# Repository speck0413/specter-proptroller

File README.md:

# Specter Proptroller

An all-in-one, open-source controller for props, animatronics and show effects. One 134 x 80 mm board takes a plug-in
microcontroller (a 30-pin ESP32 DevKit **or** a Raspberry Pi Pico / Pico W / Pico 2 / Pico 2 W; a plain Pico 2 has no firmware build yet) and gives it the I/O a prop needs:

| Block | What it does |
|---|---|
| 4 power outputs (OUT1-4) | high-side switched supply voltage, 5 A each continuous at 12-24 V (7.5 A for 5 s at low duty from idle, 10 A start-up surge under 1 s; 10 A board total); PWM dimming and soft start up to 2 A at 12 V (1 A at 24 V); LED per output |
| 2 relays (RLY1-2) | dry COM / NO / NC contacts. Rev B: **120 V AC 5 A (3 A inductive) or 28 V DC 10 A**; rev A: **≤30 V DC only** |
| Trigger inputs (TRIG1, TRIG2) | 3.5 mm TRS jacks: contact closure or a small powered sensor (3.3 V on the ring) |
| Contact outputs (CONTACT1-2; CC1-2 in scripts and code) | isolated optocoupler closures on 3.5 mm jacks, to trigger other controllers or devices: signals only, ≤30 V DC, plan on about 2 mA, tip + / sleeve − |
| Pixels | 5 V level-shifted data for addressable LED strips |
| Audio | DFPlayer Mini MP3 module (two-way UART), speaker terminal and stereo line out |
| Buttons | three on-board user buttons |
| Expansion | 3 x 11 servo-style S/V/G header (I2C, analog, spare GPIOs), RAILS power terminal for accessories |
| Power | 9-24 V DC in (barrel ≤5 A or terminal ≤10 A), on-board 5 V / 2.5 A buck, TVS protection. Ratings are for a 12-24 V supply (12 V is the primary use case); below 12 V (down to the 9 V minimum), derate: the OUT FETs see less gate drive and run hotter |

Controllers can be cascaded: a CONTACT output or a relay of one board triggers the TRIG1 / TRIG2 input of another, so one
controller can drive up to four others; ESP-NOW / Wi-Fi is the option for richer coordination.

## Getting started

New here? **[GETTING-STARTED.md](GETTING-STARTED.md)** goes from the parts on your table to a running prop with no
programming: what to buy, flashing the stock firmware from the browser (ESP32) or by copying one file (Pico W),
the sound card, wiring, and your first effect script typed on your phone. Then:

- [firmware/SHOW-SCRIPT.md](firmware/SHOW-SCRIPT.md): the effect script language (nine kinds of line), and
  [firmware/show-script-examples/](firmware/show-script-examples/) with wiring notes;
- [the Arduino library](firmware/arduino/lib/proptroller/README.md): effects in code;
- [hardware/README.md](hardware/README.md): ratings, pinout and power.
- [firmware/BARE-DEVKIT.md](firmware/BARE-DEVKIT.md): no board yet? Run the firmware on a bare ESP32 DevKit,
  ESP32-S3 DevKit or ESP32-C3 SuperMini (outputs through MOSFET or relay modules).
- [studio/](studio/README.md): **Specter Studio**, the desktop app for these boards (Windows, macOS, Linux):
  find boards, write effects as text or blocks, try them on a practice board, update firmware, copy sounds to the
  SD card. Installers are on the [releases page](https://github.com/speck0413/specter-proptroller/releases)
  (`studio-v…` tags).
- [docs/DEV-SETUP.md](docs/DEV-SETUP.md): from nothing to a running board with Specter Studio built from
  source (macOS, with Windows and Linux notes): the setup script, the clone, a USB install and a script.
- [docs/FIRMWARE-BUILD.md](docs/FIRMWARE-BUILD.md): build the firmware for each board, flash it over USB, make a
  release folder, update over Wi-Fi, and what CI does on a release tag.

## Status

This repository holds hardware rev B (relay insulation margin and air-gap slots for a 120 V AC relay rating, see
`hardware/README.md`), not yet ordered. Rev A, the first ordered design (silk "RELAYS: <=30V DC ONLY"; not yet built or
tested), differs as `hardware/README.md` describes (ratings, relay positions, errata).
A 3D-printed enclosure is in `enclosure/` (not printed yet).
Firmware: C++ on the Arduino cores with PlatformIO (`firmware/arduino`), tested on the host and in a simulator; not yet run on a
board. The desktop app, Specter Studio, is in `studio/`. Wiring guides and a build guide are in `docs/` (below).

## What is here

| Path | Contents |
|---|---|
| `hardware/board.ts` | the board, written as design intent for the [aieda](https://github.com/speck0413/ai-native-eda) toolchain (parts, nets, placement constraints, routing classes) |
| `hardware/frozen.ts`, `hardware/routes.ts` | the reviewed part placement and locked routing, so every build reproduces the same board |
| `hardware/lib/parts.ts` | the parts this board uses (KiCad footprints, LCSC numbers, pad maps checked against datasheets) |
| `hardware/requirements.yaml` | requirements with ids traced by the build |
| `hardware/README.md` | ratings, GPIO map, power budget, copper sizing, test pads and first-board checks |
| `enclosure/` | the 3D-printed enclosure: OpenSCAD model, `design.toml` with every size, Bambu Studio projects, build and check tools |
| `GETTING-STARTED.md` | from a new board to a running prop, no programming |
| `firmware/` | the firmware (`arduino/`), the protocol (`PROTOCOL.md`), flash maps, the phone web UI (`web/`) and its browser tests (`web-test/`), golden sets and example show scripts |
| `studio/` | Specter Studio, the desktop app (Tauri: Rust device layer in `core/`, React app in `src/`, Playwright tests in `tests/e2e/`); it builds its practice board from `firmware/` and bundles the firmware library and the wiring guides. See [studio/README.md](studio/README.md) and [studio/docs/BUILDING.md](studio/docs/BUILDING.md) |
| `.github/workflows/` | `firmware.yml`: firmware host tests, board builds, examples, simulator and phone-page browser tests (on changes to `firmware/`); `firmware-release.yml`: on a tag `v<firmware/VERSION>`, builds the stock firmware (ESP32 DevKit, Pico W, Pico 2 W, and the bare devkits), drafts a GitHub Release with the update and first-flash images and `proptroller-firmware.json`, and publishes the browser flasher to GitHub Pages; `studio.yml`: Studio's tests and e2e (on changes to `studio/` or `firmware/`), the installers (on changes to `studio/`), and on a tag `studio-v<version>` the installers on that tag's release |
| `docs/` | wiring guides (interactive 3D pages, written pages, videos), the case build guide, switching AC loads, developer setup with Specter Studio (`DEV-SETUP.md`), building and flashing the firmware (`FIRMWARE-BUILD.md`) |
| `tools/` | `setup.sh` (firmware setup; `--dev` for the developer checks; Studio has its own, `studio/scripts/setup.sh`), bootstrap, JLC order packages (with rotation corrections), routing helpers |

The generated KiCad project (`hardware/kicad/`: board, schematic, rules, symbol library, build records) and the order files
(`hardware/fab/`: gerbers zip, BOM, CPL, three JLC packages) are committed, so you can open or order the board without building it.
Regenerating takes a few minutes and runs `tools/portable_paths.py` so the files carry no machine-specific paths.

## Developer quick start (VS Code)

For changing the firmware itself. To use a board, [GETTING-STARTED.md](GETTING-STARTED.md) is enough; to write
effects in code, start with [the library's README](firmware/arduino/lib/proptroller/README.md).

1. Clone and set up (Linux or macOS; Windows: see [Windows](#windows) below):
   ```sh
   git clone https://github.com/speck0413/specter-proptroller.git && cd specter-proptroller
   tools/setup.sh            # PlatformIO, a host compiler, the board packages; asks before sudo
   tools/setup.sh --dev      # optional: also clang-tidy, cppcheck, fuzzers, browser-test tools
   ```
   It offers (asking first) to put `pio` on your PATH and, on Linux, the serial-port access (the `dialout`
   group and PlatformIO's udev rules; log out and in afterwards).
2. Open it: `code spectre-proptroller.code-workspace`, then click **Install** when VS Code offers the
   recommended extensions (PlatformIO IDE, C/C++, EditorConfig, Markdown lint, spell checker, WSL).
3. Wait for PlatformIO to finish loading (status bar), then **Terminal > Run Task**:
   - **Native unit tests**: the host tests (no board needed).
   - **Host simulator**: a simulated board; open <http://localhost:8080/> for its phone page.
   - **Build all boards**: ESP32 DevKit, Pico, Pico W, Pico 2 W, and the bare devkits (ESP32, ESP32-S3, ESP32-C3 SuperMini).
4. Flash a board (USB):
   - ESP32 DevKit: `cd firmware/arduino && pio run -e esp32dev -t upload`
   - Pico (no Wi-Fi): `cd firmware/arduino && pio run -e pico -t upload` (the first time, hold BOOTSEL while
     plugging it in). It is updated over USB only.
   - Pico W / Pico 2 W (first time): run the task **Pico W / Pico 2 W first-flash file**, hold BOOTSEL, plug in,
     copy `firmware/arduino/.pio/build/picoboot-pico-w/flash.uf2` (Pico 2 W: `picoboot-pico2-w`) to the drive.
     After that, update over Wi-Fi from the board's page.
5. Change something: your own firmware starts from `firmware/arduino/workspace-template/`; effects without code are show
   scripts (`firmware/show-script-examples/`). Writing sketches: [the library's README](firmware/arduino/lib/proptroller/README.md);
   how the firmware is built and tested: [firmware/arduino/README.md](firmware/arduino/README.md).

### Windows

Two ways, both with VS Code:

- **Native (simplest for building and flashing boards):** install [VS Code](https://code.visualstudio.com/), then the
  **PlatformIO IDE** extension (it installs PlatformIO and its Python by itself), and open
  `spectre-proptroller.code-workspace`. The tasks **Build all boards** and **Pico W / Pico 2 W first-flash file** and
  PlatformIO's own Upload button work in it. Install the USB driver your ESP32 DevKit needs (Silicon Labs CP210x or
  WCH CH340). The host unit tests and the simulator also need a C++ compiler for Windows (for example MSYS2's
  MinGW-w64 g++ on PATH; the simulator is `pio run -e sim_win`, without MQTT); the tasks that are shell scripts (static check, fuzzers, browser tests, QEMU, golden
  files) need WSL 2.
- **WSL 2 (everything):** install WSL 2 with Ubuntu (`wsl --install` in an administrator PowerShell), install the
  **WSL** extension in VS Code, open the folder with **WSL: Open Folder in WSL**, and run `tools/setup.sh` in its
  terminal. WSL does not see USB by itself: install [usbipd-win](https://github.com/dorssel/usbipd-win) in Windows,
  then `usbipd list`, `usbipd bind --busid <id>` (once, administrator) and `usbipd attach --wsl --busid <id>` each
  time the board is plugged in.

### If something goes wrong

- **The page says `rolled_back`**: the new firmware did not pass its self-check and the board went back to the
  one before. Your settings are as they were; try the update again or report it.
- **A Pico W that will not stay up** (restarts every few seconds): flash it again over USB (hold BOOTSEL, copy
  the first-flash file). Re-flashing keeps the settings, shows and script; if it still restarts (a saved setting
  such as an unreachable Wi-Fi), erase everything as below and set it up again.
- **Start over, erasing everything** (settings, Wi-Fi, shows, script): Settings, Factory reset on the page, or
  over USB: Pico `picotool erase` (then flash again), ESP32 `pio run -e esp32dev -t erase` (or
  `esptool.py erase_flash`) and flash again.

## Specter Studio from source

```sh
git clone https://github.com/speck0413/specter-proptroller.git && cd specter-proptroller/studio
scripts/setup.sh          # Node.js, Rust, PlatformIO, Tauri's system parts; npm ci and the practice board
npm run tauri dev         # the desktop app
```

Windows uses `scripts\setup.ps1`. The step-by-step version is [docs/DEV-SETUP.md](docs/DEV-SETUP.md); tests,
desktop builds and the layout are in [studio/README.md](studio/README.md). Studio needs no submodule (the `aieda`
submodule is for the hardware build only).

## Releases

One repository, two kinds of tag:

| Tag | Workflow | Release |
|---|---|---|
| `v<firmware/VERSION>`, e.g. `v0.1.0-rc.3` | `firmware-release.yml` | a draft "Firmware v…" release with the images and `proptroller-firmware.json` (published by hand), and the browser flasher |
| `studio-v<version>`, e.g. `studio-v0.1.0-rc.3` (the version in `studio/package.json`, `studio/src-tauri/tauri.conf.json` and `studio/Cargo.toml`) | `studio.yml` | a "Specter Studio …" release with the installers and `SHA256SUMS.txt` |

A version with a suffix (`-rc.3`) makes a pre-release. Studio's firmware updates look only at releases that
carry `proptroller-firmware.json`, so Studio's own releases never count as firmware; GitHub's "Latest" label goes
to whichever full release is newest, so link the firmware by its tag. Details:
[docs/FIRMWARE-BUILD.md](docs/FIRMWARE-BUILD.md) (section 6) and [studio/docs/BUILDING.md](studio/docs/BUILDING.md).

## Build (hardware)

Requires KiCad 10 (with `kicad-cli`), Node.js, Python 3 and Java (for Freerouting).

```sh
git clone --recursive https://github.com/speck0413/specter-proptroller.git && cd specter-proptroller
tools/bootstrap.sh        # aieda submodule, its Node deps, Freerouting
make typecheck
make build                # KiCad project in hardware/kicad/ (about 4 minutes)
make fab order            # gerbers in hardware/fab/, JLC BOM/CPL packages in hardware/fab/order/
```

Always check JLC's placement preview before ordering.

The committed `hardware/kicad/proptroller.kicad_pcb` is the reference board. Every signal and power net is locked (`routes.ts`) and the
placement is pinned, so a rebuild reproduces the same tracks and vias with the toolchain it was made with: KiCad 10.0.6, Freerouting 2.5.0
(`tools/freerouting.pin`), aieda v0.2.0-1-gcd1f38a (submodule). Other tool versions may change the GND fanout or pour fill: compare before replacing it.

## Wiring guides

New to wiring? [docs/wiring-guides/](docs/wiring-guides/README.md) has a starter kit (a button, a motion sensor, a lamp,
a fan, a pixel strip and a speaker on one desk) and short guides for the common hookups, each as an interactive 3D page
with narration ([docs/wiring-guides/html/index.html](docs/wiring-guides/html/index.html), works offline), a written page,
and a renderable video. Assembling the board into its case: [docs/build-guide/](docs/build-guide/index.html) (written for rev A and an earlier case:
where it differs, `hardware/README.md` and `enclosure/README.md` are right).

## Safety

Read **[SAFETY.md](SAFETY.md)** first: the project is provided as-is, with no warranty and no certification, and you build
and use it at your own risk.

The board is powered from **low-voltage DC**: use a listed power supply with its own over-current protection (≤10 A); the board has
no fuses. The recommended way to switch AC loads is **off the board**, with a listed relay-controlled outlet box driven at low voltage
([docs/ac-control.md](docs/ac-control.md)). Only the rev B relays may switch AC directly, up to **120 V AC 5 A (3 A inductive)** each, only
from a GFCI-protected outlet, with a 5 A fuse in each relay's COM wire, and in the AC case with its earth leads on both earth holes (H2, H3). That rating rests on the relay's own insulation and a design margin
(≥3.0 mm copper clearance and air-gap slots around the relay contacts), not a certification; fog fluid residue, condensation and dust
degrade it over time, so keep the board clean and dry (`hardware/README.md`). Rev A relays are rated ≤30 V DC only: **AC on rev A relays is experimental, for prove-out only, not considered safe, and recommended against until rev B**.
Every other terminal, and every 3.5 mm jack, is low-voltage DC only. The board does not measure or limit current: keep each load
within its terminal's rating ([hardware/README.md](hardware/README.md)).

## License

MIT, see [LICENSE](LICENSE). The licence covers everything in this repository: the software (firmware, Specter
Studio, tools, web page), the hardware design files (`hardware/`, `enclosure/`) and the documentation. See also [SAFETY.md](SAFETY.md).

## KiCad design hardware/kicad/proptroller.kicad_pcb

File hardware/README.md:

# Spectre Proptroller board (rev B): ratings, pinout and power

134 x 80 mm, 2 layers. Silkscreen: "SPECTRE PROPTROLLER rev B" (rev A, the first ordered design, differs as this page says; this repo holds rev B). Plug-in MCU: a 30-pin ESP32 DevKit **or** a Raspberry Pi Pico family
board (never both). The bottom silkscreen carries a short version of this page.

Provided as-is, with no warranty and no certification; you build and use it at your own risk: read
[../SAFETY.md](../SAFETY.md) before wiring anything, and above all before mains on a rev B relay.

## Ratings at a glance

Ratings are for a **12-24 V supply** (12 V is the primary use case). Below 12 V (down to the 9 V minimum), derate: the OUT FETs see
less gate drive and run hotter.

| Item | Rating | Limit set by |
|---|---|---|
| Input (barrel DC-005) | 9-24 V DC, **5 A** | jack rating |
| Input (5.08 terminal, parallel) | 9-24 V DC, **10 A** board total | +VIN copper (3.5 mm class), supply OCP |
| Protection | SMAJ24A TVS only; **no fuses, no reverse-polarity FET** | design choice (accepted risk AR-1, rev B): use a listed supply with OCP, ≤10 A; it shuts itself off on overload |
| OUT1-4 (rev A and B) | switched +VIN (high side, AO4485), **5 A each continuous**; **7.5 A for 5 s at ≤2 % duty, starting from idle (the FET cool)**, both at **VIN 12-24 V** (e.g. once every 6 min; pending a first-board heat test; below 12 V derate); **10 A only as a start-up surge under ~1 s**; **sum of everything ≤10 A**; barrel input ≤5 A (use the terminal input above 5 A) | FET junction temperature (thermal note below), SS56 freewheel, copper |
| OUT1-4 PWM | ≤1 A at 24 V, ≤2 A at 12 V (slow 4.7k turn-off heats the FET) | FET switching loss |
| RLY1-2 (rev B) | dry COM / NO / NC, **120 V AC 5 A resistive (3 A inductive) or 28 V DC 10 A resistive** per relay ("120VAC 5A (3A IND) / 28VDC 10A"); derate for DC motors and solenoids | SRD-05 contacts (Songle datasheet, below) and the SAF-1 insulation margin (a design margin, not a certification); no fuse. Rev A: **≤30 V DC only** (table below) |
| +5V buck (TPS54360B) | **2.5 A** continuous | inductor, catch diodes, thermal |
| +3V3 | from the MCU module's regulator, **0.1 A** for board use | DevKit AMS1117 / Pico RT6150 headroom |
| RAILS out (5.08 5P) | VIN 3 A, 5V 0.1 A, 3V3 0.05 A | daisy-chain feed for a small accessory, not a second board |
| PIXEL | 5 V, ≤1 A from the board (≈16 WS2812 at full white); inject 5 V for longer strips. **No bulk capacitor on the board**: fit 470-1000 µF, ≥6.3 V across +5V / GND at the strip input, and plug or unplug the strip only with power off. The data output is inverted (2N7002 stage): the firmware inverts it | +5V budget |
| SPK | DFPlayer amplifier output, 3 W max into 4 Ω (bridge-tied: never ground either wire) | DFPlayer |
| TRIG1 / TRIG2 | 3.5 mm TRS: tip = input (3.3 V logic, closes to sleeve = active LOW), ring = 3V3 via 220 Ω (≤15 mA for a powered sensor), sleeve = GND | GPIO, 220 Ω |
| CONTACT1-2 | isolated optocoupler output (LTV-217) across tip (+) / sleeve (−): **≤30 V DC, ≤50 mA absolute maximum**, polarity matters; **count on about 2 mA** switched (note below) | LTV-217 (IC 50 mA, VCEO 70 V abs; CTR at the board's LED drive) |

**CONTACT1-2 current.** 50 mA is the LTV-217's absolute maximum, not what it is guaranteed to pass. The board drives the opto LED
with about 9 mA from an ESP32 and about 5-6 mA from a Pico (the RP2040 / RP2350 pads default to 4 mA drive and the firmware sets
none). Saturated (VCE(sat) 0.4 V max at IF 8 mA, IC 2.4 mA), the guaranteed current is about 2.4 mA; the higher figure of about
4 mA (50 % minimum CTR) holds only with about 5 V left across the opto. **Count on about 2 mA**; for anything that draws more, use an
OUT or a relay (`../docs/ac-control.md`, methods 1 and 2).

## Relay contacts: ratings and insulation (rev B, SAF-1)

| Board | Relay contact rating | AC |
|---|---|---|
| rev B (silk "rev B") | **120 V AC 5 A** resistive, **3 A** inductive, or **28 V DC 10 A** resistive per relay: "RELAYS: 120VAC 5A (3A IND) / 28VDC 10A" (owner 2026-10-20; on the silk at 1.5 mm, top and bottom); derate for DC motors and solenoids | yes, on the SAF-1 margin below, behind a GFCI outlet |
| rev A (the first ordered design, silk "RELAYS: <=30V DC ONLY") | **≤30 V DC only**, 10 A resistive; derate for DC motors and solenoids | **Not recommended.** AC on rev A relays is experimental, for prove-out only, not considered safe, and recommended against until rev B |

**Source:** Songle's own SRD (T73) datasheet, V1 (songlerelay.com, `srd-t73-relay-290486.pdf`, 2025), and LCSC's copy for C35449
(`datasheet.lcsc.com/datasheet/pdf/9ddfe54b7529126320ff1ddcabf6bab7.pdf`, 2016 Chinese edition; same figures). Resistive contact rating
7 / 10 / 15 A 250 VAC / 28 VDC and 10 A 125 VAC; maximum switching 277 VAC / 30 VDC, 15 A, 2770 VA / 300 W; the maximum-switching curve
holds Form C ("AC (C)", "DC (A,C)") at 10 A up to 277 VAC and 30 VDC. UL (E167996): 10 A 125 VAC, 3 A 125 VAC inductive, 15 A 125 VAC on
NO only. The relay body of C35449 is marked 10A 250VAC / 10A 125VAC / 10A 30VDC / 10A 28VDC. The sheet gives no DC inductive figure, so
none is quoted: derate for DC motors and solenoids (and fit the flyback diode at the load). Dielectric strength 1500 VAC for 1 min coil to
contacts, 1000 VAC for 1 min across open contacts; insulation resistance 100 MΩ at 500 VDC. The board's 5 A at 120 V AC is the owner's
derating of the 10 A figure (2026-10-20); 3 A inductive is the UL 3 A 125 VAC inductive figure, and 28 V DC is the sheet's rated DC voltage
(30 VDC is only its maximum switching voltage).

The SRD-05VDC-SL-C relay bodies say 250 VAC; the board's AC rating is 120 V and rests **first on the relay's own coil-to-contact
insulation** (1500 VAC for 1 min per the datasheet, which claims no reinforced insulation: treat it as basic, a single barrier), then on the
layout below. The layout is a design margin, **not** a creepage/clearance design to a safety standard and **not** a certification. There is
no fuse on the board (accepted risk AR-1). In the enclosure's AC case a screwed mains-bay cover with a hood over J_R1/J_R2 covers the
relay terminals (finger protection only, not a rated enclosure: `../enclosure/README.md`, "AC case").

- **GFCI.** Plug anything mains-powered that runs through a relay into a GFCI-protected outlet. The venue's GFCIs are the
  backstop for an earth-leakage fault only: a GFCI does **not** trip on a line-to-neutral overload or short. The board has no fuse and no
  other protection on the relay side.
- **Fuse each relay.** Put a **5 A inline fuse in each relay's COM wire** whenever a relay switches AC, as a discrete inline fuse
  holder you add, off the board (the board has no fuse by owner decision, AR-1). Preferred: switch AC with an outlet box that has
  its own relays (`../docs/ac-control.md`), so the board's relays stay low voltage.
- **One relay on mains means both.** If either relay carries mains, treat **both** relays' wiring and terminals as mains: the 3.05 mm gap
  between the two contact islands is the only barrier between them.
- **Disconnect first.** Unplug the relay's mains side before plugging in USB to the MCU board or servicing the board.
- **Terminals.** Fitted relay screw terminals (J_R1 / J_R2) must be rated **≥250 V, ≥10 A and UL-recognised**.
- **Mains never goes on a 3.5 mm jack.** The DC enclosure brings RLY1 / RLY2 out on 3.5 mm TRS jacks (**tip = NO, ring = NC, sleeve =
  COM**); through those jacks the relay rating is limited by the jack (the figure is in `enclosure/README.md`), low-voltage only. AC loads use
  the AC case variant (outlets, rev B only) or, preferred, an off-board relay-controlled outlet: [docs/ac-control.md](../docs/ac-control.md).
- **Keep it clean and dry.** Surface contamination (fog fluid residue, condensation, dust) degrades the insulation between
  the relay contacts and the low-voltage copper over time. Keep the board in its closed box away from fog output, let it
  dry out if it has been wet, and clean off any residue with the power off.
- Each relay's contact island (COM, NO, NC: their pads, terminal pins and tracks) keeps **≥3.0 mm**
  of copper clearance to every other net on both layers, including the GND pours, and the two islands keep ≥3.0 mm from
  each other. A KiCad custom DRC rule in `board.ts` checks it (DRC 0 errors), and a measurement of the routed board with the KiCad
  Python API gives the minimum quoted under "Latest build" below. 3.0 mm is as far as this footprint goes: its COM pad is only
  3.2-3.3 mm from the coil pads.
- **Air-gap slots.** A non-plated routed slot, **1.2 mm** wide, sits between COM and each coil pad of each relay and runs 1 mm
  past both pads (four slots, `b.slot(between(...))` in `board.ts`, listed by `bin/aieda q hardware/board.ts slots`). JLC
  mills slots to ±0.2 mm, so the finished slot never drops under its 1.0 mm minimum; about 1.0 mm of board is left to each pad.
- To get there, rev B moved the relays 18.1 mm apart (was 17.0) and moved the buck output capacitors C_BO1/C_BO2 and test pads TP2/TP5 west. (The 2026-10-21 buck-ground fix then moved C_BO1/C_BO2 west of L_BK and the input caps C_BI1/C_BI2 upright beside U_BK; see Layout and build.)
  PWM3 and USER2 now run along the front edge south of the relay terminals. The +5V and +VIN_BK runs over K1 moved north, and D_C1 moved
  between the relays (turned 180°).
- Rev B has no protection parts on the relay contacts. The rev A NO→GND flyback footprints (D_FB1/D_FB2) and the DNP RC snubber footprints
  (R_SN1/R_SN2, C_SN1/C_SN2) are gone: the independent review measured the COM track 0.625 mm from the bare snubber pads, below IPC-2221 B2
  (about 1.25 mm for 151-300 V), and a snubber fitted on an AC load is a hazard. Fit the flyback diode, or a snubber if needed, **at the load,
  DC loads only**.

## Earth bond (rev B, SAF-2)

- **Two bonding points.** The front-west hole **H3 (4, 76)** and the back-east hole **H2 (130, 4)**, both marked **EARTH** on both faces,
  are plated: a 6.4 mm copper pad on both faces, on **GND**. H1 and H4 are unplated. In the AC case, run the green earth wire (from the
  receptacle's green screw, or from a lever connector on the cord's earth) to **both** holes, each with an **M3 ring terminal** under the
  screw head, seated flat on the pad. At H3 point the tongue off the west or south edge (away from the TRIG1 jack's pads).
- **Why two.** The relay row (with its SAF-1 pour pullbacks) and the MCU nest split the board's GND into a west part and an east part on both
  layers. H3 bonds the west part, which holds the GND next to the relay contacts, where an on-board insulation fault (island tracking,
  relay coil-to-contact breakdown) enters GND. The main GND body in the east (power entry, OUT returns, DFPlayer) reaches H3 through no
  more than **3.1 mm** of copper even with every reroutable track taken out (measured), short of the 5.5 mm target, so it gets its own
  hole, H2.
- **Solid bond, no jumper** (owner 2026-10-21, after the independent reviews). Each pad joins both GND pours all round its edge (no thermal
  spokes) and the other layer through its own plated barrel plus a ring of five 0.4 mm GND vias. The rev B solder jumper SJ_E is gone: its
  0.6 mm bridge and thin tracks melt at about 28-127 A²s, near a 5 A fuse's I²t, so it could open before a fault cleared.
- **Measured** (the review's raster / max-flow min-cut on the routed board, 1 oz, vias counted at π × drill × 25/35): relay-adjacent GND
  to H3 **9.7 mm**, main GND body to H2 **25.6 mm** (target ≥5.5 mm, 0.19 mm²). With S = width × 0.035 mm that is about
  **9.7 kA²s** and **68 kA²s** before the narrowest copper melts (Onderdonk, adiabatic); the target is about 3 kA²s.
  Split by relay (both holes earthed, as the AC case has them): GND next to K1 to the earth holes 10.3 mm (9.7 mm to H3 alone), GND next
  to K2 6.9 mm, about 5 kA²s. K2's side reaches H3 alone through only 1.9 mm, part of it lying in the east GND, so **both earth leads are
  needed** whenever a relay carries mains; with only H3 earthed, K2's side is below the 5.5 mm target. The holes are 34.5 mm (H3) and
  74.3 mm (H2) from the nearest island copper.
- **Earthed or not** depends only on the ring terminals. With them fitted, an insulation fault from a mains-wired relay to the low-voltage
  side (GND, the jack sleeves, the MCU module) has a path to earth, and the 5 A COM fuse, the breaker or the GFCI clears it. Leaving them off
  (board GND not earthed) is allowed **only when no relay carries mains** (the DC enclosure, or relays switching low voltage).
- This is a design margin, not a protective-earth conductor sized to a safety standard. Both holes are more than 3.0 mm from both relay
  contact islands (the SAF-1 rule covers every net).
- **Audio hum.** With GND earthed and LINE OUT feeding an amplifier that is itself earthed, the two earths can make a ground loop and a hum.
  The fix is a **3.5 mm ground-loop isolator (transformer type) on LINE OUT**. More supply filtering does not fix a ground loop; the
  DFPlayer's supply filter (FB_DF, 100 µF + 100 nF, the Schottky) stays as it is. The SPK output is bridge-tied and never touches GND, so
  it is not part of the loop. There is no LINE OUT ground-lift resistor on the board (owner 2026-10-20): the plug-in isolator is the fix.

## Copper sizing basis

1 oz outer copper, sized for a **20 °C rise** (IPC-2221 external), each width divided by 0.8 for JLC's ±20 % etch tolerance:

| Path | Current | Copper | IPC-2221 width at 20 °C | Used |
|---|---|---|---|---|
| +VIN trunk + FET bus (J_IN → x 97.5 → y 49.3) | 10 A | F only | 4.72 mm → **5.9 mm** | 5.9 mm, locked |
| FET source stubs, OUT1-4 drain → terminal | 5 A each | F | 1.82 mm → **2.3 mm** | 2.3 mm |
| Relay NO / COM / NC (relay pad → terminal) | 10 A DC (5 A AC) | F **and** B in parallel, 5 A each | 2.3 mm per layer | 2.3 mm × 2, locked |
| RAILS +VIN | 3 A | F | 0.9 mm → 1.1 mm | 2.3 mm |
| Buck input +VIN_BK (through FB_BK) | 1.55 A at 9 V in | any | 0.5 mm | 0.8 mm (1.2 mm +VIN into FB_BK) |
| +5V, BK_SW | 2.5 A | any | 0.7 mm → 0.87 mm | 0.9 mm (J_RAIL / J_PX / SJ_V / FB_DF / K2 trunk locked) |
| +5V_MCU (DevKit VIN / Pico VSYS) | 0.8 A | any | 0.25 mm → 0.3 mm | 0.5 mm, locked |

The aieda oracle checks current at a fixed 10 °C rise and treats each layer's track on its own, so its `amps` / `width` rows for +VIN,
OUT1-4 and R1/R2_* fail by design. This table is the hand calculation that replaces them (a toolchain limitation). A 20 °C rise in a
50 °C box puts the hottest copper near 70 °C, well inside FR-4 (TG 135) and the 105 °C terminal ratings.

## OUT1-4 thermal basis (rev A and rev B)

The old "7.5 A for 0.5 s" was an inrush allowance carried from the original F-2 / IF-5 requirement, not a part limit. The rating
(owner 2026-10-20, restricted after the independent review) rests on this estimate of the AO4485 junction temperature (Tj) in a 50 °C box.
None of it is measured yet.

- **Datasheet (AO4485):** RDS(on) max 15 mΩ at VGS −10 V, 20 mΩ at −4.5 V, 23 mΩ at −10 V and Tj 125 °C (a 1.53× hot ratio).
  RθJA 40 °C/W for t ≤ 10 s and 75 °C/W steady, both on 1 in² of 2 oz copper; RθJL 24 °C/W.
- **This board:** about 0.1 in² of 1 oz drain copper per FET, far less than the datasheet's test board. The figures used here, Zθ(5 s)
  about **50-60 °C/W** and RθJA about **75-100 °C/W** steady, are **unverified estimates**, not datasheet or measured values.
- **Gate drive is −VIN/2**, so RDS(on) (max, cold / hot) depends on the supply:
  - 9 V in, VGS −4.5 V: about 20 mΩ cold, about 31 mΩ hot.
  - 12 V in, VGS −6 V: about 18 mΩ cold, about 27 mΩ hot.
  - 24 V in, VGS −12 V: about 15 mΩ cold, about 23 mΩ hot.
- **5 A steady** (hot RDS(on), 75-100 °C/W): 12 V 0.68 W, Tj 101-118 °C; 24 V 0.58 W, Tj 93-108 °C; **9 V 0.78 W, Tj 108-128 °C**.
  Under the 150 °C maximum at every input voltage, so 5 A continuous stands.
- **7.5 A for 5 s from idle** (FET at ambient, hot RDS(on) for margin, 50-60 °C/W): 12 V 1.52 W, Tj 126-141 °C; 24 V 1.29 W,
  Tj 115-128 °C; **9 V 1.74 W, Tj 137-155 °C**, which can pass 150 °C: hence the ratings are stated for **12-24 V**.
- **7.5 A for 5 s starting from 5 A steady** (12 V): Tj **147-164 °C**, over the maximum: hence **"starting from idle"**. The ≤2 % duty
  (e.g. once every 6 min) is what lets the FET cool back to idle between pulses.
- **10 A for 5 s:** 12 V 2.7 W, far too hot; 10 A is a start-up surge under ~1 s only. (The datasheet allows 12 A for 10 s on its own
  test board.)
- Copper: the 2.3 mm single-layer OUT stub at 7.5 A is about 34 °C rise steady (IPC-2221), less over 5 s.
- So the OUT ratings are stated for **VIN 12-24 V** (12 V is the primary use case). The 9 V figures above are the reason for the derating line:
  below 12 V (down to the 9 V minimum), derate: the OUT FETs see less gate drive and run hotter.
- The 7.5 A / 5 s figure is **pending the first-board heat test** (below); if the board passes only from idle, the rating stays "from idle".

## +5V budget (2.5 A buck)

| Load | Typical | Peak | Note |
|---|---|---|---|
| ESP32 DevKit (Wi-Fi on) | 0.15 A | 0.5 A | radio bursts; Pico W is about 0.1 / 0.3 A |
| DFPlayer Mini | 0.05 A | 0.8 A | audio peaks at full volume into 4 Ω |
| Relay coils SRD-05 | 0.072 A each | 0.144 A | both on |
| Relay + output LEDs | 0.02 A | 0.03 A | |
| PIXEL strip | — | ≈1.0 A | what is left: 2.5 − 0.5 − 0.8 − 0.15 ≈ 1 A |
| RAILS 5V | — | 0.1 A | |

Rule of thumb: with everything at its peak the 5 V rail is full. Longer pixel strips take their own 5 V supply
(join only DATA and GND to the board).

## Where the current goes on +VIN

+VIN = OUT1-4 loads + the buck input (2.5 A × 5 V / VIN / 0.9 ≈ 1.2 A at 12 V, 0.6 A at 24 V) + RAILS VIN.
Keep the total under the supply's rating and **under 10 A**. Example at 12 V: 4 × 2 A solenoids (8 A) + buck at
full load (1.2 A) = 9.2 A.

## Test pads (pogo)

| Pad | Net | Note |
|---|---|---|
| TP1 | +VIN | behind the input terminal |
| TP2 | +5V | at the buck output |
| TP3 | +3V3 | near the RAILS terminal |
| TP4 | DF_BUSY | under the DFPlayer: reachable with the module out |
| TP5 | GND | at the buck |

## GPIO map

| Function | ESP32 DevKit GPIO | Pico GPIO |
|---|---|---|
| OUT1 gate (PWM) | 23 | GP15 |
| OUT2 gate (PWM) | 22 | GP14 |
| OUT3 gate (PWM) | 21 | GP12 |
| OUT4 gate (PWM) | 19 | GP11 |
| TRIG2 input (back TRS) | 18 | GP10 |
| USER3 button | 5 | GP9 |
| DFPlayer RX (MCU TX) | 17 | GP8 |
| I2C SDA (expansion S1) | 4 | GP4 |
| I2C SCL (expansion S2) | 16 | GP5 |
| expansion S4 | 15 | GP3 |
| USER1 button | 13 | GP28 |
| USER2 button | 14 | GP27 |
| CONTACT1 opto | 27 | GP22 |
| RLY2 coil driver | 26 | GP21 |
| RLY1 coil driver | 25 | GP20 |
| PIXEL data (inverted by the level shifter) | 33 | GP19 |
| CONTACT2 opto | 32 | GP18 |
| expansion S5 (input only on ESP32) | 35 | GP17 |
| TRIG1 input (front TRS) | 36 | GP16 |
| analog in (expansion S3) | 39 | GP26 |
| expansion S6 = DFPlayer TX (MCU RX) | 34 | GP7 |

Pico-only expansion pins (S7-S11): GP0, GP1, GP2, GP6, GP13. The DevKit status LED is GPIO2. GPIO34-39 are input-only on the ESP32.
DFPlayer UART: ESP32 UART2 TX on GPIO17, RX on GPIO34 (GPIO matrix); Pico UART1 TX on GP8, RX on GP7 via a PIO UART. Header pin S6
carries the DFPlayer's TX: monitor it, never drive it.

## Orientation

- MCU nest: antennas at the **west** edge (DevKit antenna overhangs it), USB toward the board centre. DevKit EN (pin 1) is the
  west pin of the south socket row; Pico pin 1 (GP0) is the east pin of the north Pico row. Never fit both.
- DFPlayer: pin 1 (VCC) at the west end of the south row; the microSD slot (between pins 8 and 9) faces the **east** edge.

## Layout and build

- Source of truth: `board.ts` (intent: parts, nets, placement constraints, routing classes), with `frozen.ts` (reviewed part poses) and
  `routes.ts` (locked routed copper). The KiCad project, gerbers, BOM and pick-and-place are generated by `bin/aieda build` / `bin/aieda fab`
  and committed (`kicad/`, `fab/`). In KiCad the schematic and board are one linked project (every footprint carries its symbol's path);
  KiCad's own parity check reports field-only differences (LCSC fields, BOM-exclusion flags, deliberate no-connect pins), no net errors.
- 2 layers, 1 oz, 134 x 80 mm, JLCPCB Economic assembly. Every signal and power net is locked, so a rebuild reproduces the same copper
  (only the GND pour and its fanout are left to the router).
- Latest build (rev B, aieda cd1f38a, 2026-10-21: buck ground rejoined, earth bonds at H2 and H3, bottom silk off the vias): 0 DRC errors
  (including the SAF-1 island rule and the slots), 0 unconnected; `check slot` passes for all four slots (nearest copper 0.8 mm, the K1 coil
  feed). Measured contact-island clearance (KiCad Python API on the routed board): minimum **3.05 mm on F and on B** (K1 NC to K2 NO 3.054 mm;
  K1 COM to the +5V coil feed on B, 3.052 mm). Every bottom-silk text keeps at least 0.15 mm from via copper, pads and holes (the review's
  silkall.py). Of the failing checks:
  - the current checks (`amps` / `width`) assume a 10 C rise on one layer; this board is sized for 20 C, with 10 A paths on two layers (table
    above);
  - `plane-current GND B` and `GND F` report **SPLIT**, and that is real, not cosmetic: on its own neither layer joins every GND terminal
    (the MCU nest has no F pour, and the relay row's SAF-1 pullbacks and the nest's tracks cut both layers). Followed across the vias
    (tried with the class's `parallel` option) GND is whole, but its narrowest path to the nest decouplers is a 0.2 mm plane-fanout stub, so
    that row fails too and was left off. The fault-current paths that matter are measured as min-cuts instead (Earth bond, above): relay side
    to H3 9.7 mm, main body to H2 25.6 mm, main body to H3 only 1.9 mm, which is why there are two earth holes;
  - non-45-degree segments at pad entries are cosmetic.
- Buck ground (rev B, 2026-10-21 review): the input caps C_BI1/2 stand upright beside U_BK pin 2 (VIN pads in a row, GND pads south), the
  output caps C_BO1/2 sit west of L_BK pad 2 (GND pads west), and one solid-connect F ground area joins their grounds, the copper under
  L_BK between its pads, the catch-diode anodes and the PowerPAD. The rev B layout before this fix had them split: the +5 V output ran round
  the input caps on F (L_BK → x 34.4 → y 60.4 → x 42.05) and USER2 ran down B at x 34.84, and with the K1 pour pullback they fenced the cap
  grounds off (one 0.39 mm neck). The +5 V output now drops to B through four vias after C_BO and runs north at x 35.5, beside the K1 moat;
  USER2 runs down B at x 36.45. Measured min-cuts (review method): input-cap GND to the catch-diode anodes **4.1 mm on F** (was 0) and
  **4.8 mm on F + B** (was 0.4 mm); output caps to the diodes 7.8 mm; input caps to the PowerPAD on F only 0.9 mm (the package's pin rows
  leave the PowerPAD two narrow F exits; its vias join it to the B plane). The F return from the input caps to the diodes still runs
  under L_BK, about 30 mm, and only C_BI1's ground via reaches the B plane under the IC (C_BI2's lands in the strip between the +5 V
  trunk and USER2), so the B plane adds little to that loop: the bench check below (SW / VIN overshoot, ripple) is the real test.
- JLC orders: upload the gerbers plus the BOM / CPL from `tools/jlc_packages.py`, which applies the rotation corrections JLC's parts need
  (checked in JLC's 3D placement preview). Inspect the placement preview before ordering.
  In JLC's gerber viewer, check that **H2 and H3 are plated and H1 / H4 are not**: all four are 3.2 mm, in one mixed-plating drill file
  (`proptroller.drl`: H2 / H3 in a plated 3.2 mm tool, H1 / H4 in a non-plated one), so check the plating, not just the size.
- Reference designators: `tools/silk_refs.py` (run by `make build`) moves each one to the silkscreen beside its part, clear of pads,
  part bodies and the relay slots. aieda v0.2's own `b.silkRefs()` skips footprint-only (`mech`) parts such as the terminals and
  sockets, so the script stays. Parts in the densest clusters keep theirs on the fab layer (listed by the script);
  the KiCad file and the fab drawing still name them.

## First-board checks

- **Rev A boards only:** run the buck bench test of the Rev A errata (24 V in, 2.5 A load, SW / VIN at the IC pins and the +5 V ripple,
  before and after the bodge) and fit the C_BI2 → D_CT2 / C_BO2 → D_CT1 ground wires unless the test shows they are not needed.
- **Buck (rev B):** at 24 V in and 2.5 A out, scope SW and VIN at the IC pins and the +5 V ripple at C_BO1 (the input and output cap grounds
  now join the catch-diode and PowerPAD ground on F; see Layout and build).
- Continuity-check one PJ-320D jack (tip / sleeve pads) and the relay NO / NC pins against the silk. Check that no relay contact pin has continuity to GND (rev B has no NO→GND diode).
- After hand-soldering: no bridges between RAILS +5V / +3V3, the expansion header +5V / GND, and DFPlayer socket pins 3-5.
- Dry-fit an ESP32 DevKit: it should clear relay K1 by about 2.8 mm. Rev B moved K1 0.9 mm west, toward the DevKit's USB end, so measure from
  the DevKit's USB shell and board edge to the K1 pins and to the J_R1 screws, and check how far the DevKit reaches east over K1. Its outline is not measured.
- DFPlayer TX level on J_DFA pin 3 should be about 3.3 V (DFRobot); confirm on clones.
- Load +5V to about 2 A (pixels plus DFPlayer playing) and check the drop at the PIXEL and RAILS terminals.
- Probe the buck's switch node and +5V ripple; check a 10 A output load path for temperature.
- **OUT heat test** (closed box, lid on), run at **12 V** (the primary case) **and at 24 V**. 9 V is not part of the pass criterion; it is
  covered by the derating line (below 12 V, derate):
  - Calibrate first: on a hotplate, measure RDS(on) of a spare AO4485 (same part, same gate drive as on the board: −VIN/2) at a known
    small current over 25-150 °C, to get an RDS(on)-to-Tj curve.
  - Load the output under test with **5 A steady** and the neighbouring OUT with 5 A too, and let it settle. Then add the pulses: **7.5 A
    resistive for 5 s every 6 min for 30 min** on the output under test.
  - Log VDS across the FET's own source and drain pins (not at the terminals, whose copper drop would read as extra RDS(on)) during each
    pulse, convert it to RDS(on) (VDS / I) and then to Tj with the calibration curve. Log the OUT terminal temperatures too (thermocouple).
  - Extrapolate to a 50 °C box: Tj(50 °C) = measured Tj + (50 °C − measured ambient), and the same for the terminals.
  - **Pass:** Tj(50 °C) ≤ 125 °C and terminals ≤ 90 °C (their rating is 105 °C).
  - If the run from 5 A steady fails, repeat it with the pulses **starting from idle** (output off between pulses, neighbour still at 5 A).
    If only that passes, the rating stays "from idle". Until a run passes, the 7.5 A / 5 s rating stays "pending".

- **Earth bond (SAF-2):** H2 and H3 each read continuity to GND. In the AC case, with the earth leads on both: GND to the receptacle's earth
  screw under 1 Ω at each hole, and the GFCI test trips.

### Relay insulation and mains checks (rev B, before any relay carries mains)

- **Insulation screen:** 500 V DC insulation tester, **≥100 MΩ** each time, from each relay island (COM + NO + NC tied) to all low-voltage
  nets tied together (GND, +VIN, +5V, +3V3 and the MCU sockets), from island to island, and across each relay's open contacts. Repeat after a
  fog or humidity soak. This is a **screen, not a 1500 VAC withstand (hi-pot) test**: it finds contamination and gross faults, it does not
  prove the insulation withstands a mains surge.
- **Slots:** check all four air-gap slots are present and caliper each width: **≥1.0 mm**.
- **Heat run:** 1 h with **both relays energised and both loaded at the same time** (5 A resistive each, 120 V AC), in the closed box,
  logging the screw-terminal and relay-pin temperatures. Songle's temperature note assumes relays at least 10 mm apart; K1 and K2 bodies
  are only 2.6 mm apart (the 18.1 mm is their pitch), so each heats the other.
- **GFCI:** press the test button of the GFCI outlet the rig uses and confirm it trips and the load goes off.
- **Inductive switching:** switch a real fog machine remote (inductive) many times, on the GFCI outlet with a 5 A fuse in each relay's COM wire, and check
  the contacts and the remote.

## Rev A errata (the first ordered design)

- **Buck ground split.** On rev A the input-cap and output-cap grounds (C_BI1/2, C_BO1/2) reach the catch diodes (D_CT1/2) and U_BK only
  through a 0.39 mm pour neck at (32.5, 74.9) and one 0.3 mm GND via at (38.5, 74.45): about 1.1 mm of copper (min-cut), and the
  input-cap → catch-diode loop detours about 50 mm. Rev B fixes it in the layout (below). There is no rev A safety erratum: rev A has no earth
  bond, and its other GND necks are wide (≥6.7 mm).
- **Bodge** (top side): short heavy wires, 20-22 AWG or braid, from **C_BI2 pad 2 to D_CT2 pad 2** (about 18 mm) and from **C_BO2 pad 2 to
  D_CT1 pad 2**. Do not tie them to the R_RT or C_CF (quiet) grounds.
- **Bench test before deciding it is optional:** at 24 V in and a 2.5 A load, scope SW and VIN at the IC pins and measure the +5 V output
  ripple, before and after the bodge. If the SW / VIN overshoot stays well under the TPS54360B's 65 V absolute maximum and the ripple is
  acceptable without it, the bodge is optional; otherwise fit it on every rev A board.

## Where things are

- Back edge (north): PIXEL, TRIG2 jack, CONTACT1-2 jacks, RAILS, power in (barrel + terminal), SPK.
- Front edge (south): TRIG1 jack, RLY1-2, OUT1-4.
- East: DFPlayer (card slot at the edge), LINE OUT jack, USER1-3.
- West: MCU antenna end. M3 holes in all four corners; the front-west one (H3) and the back-east one (H2) are plated, on GND: the EARTH bonding points.

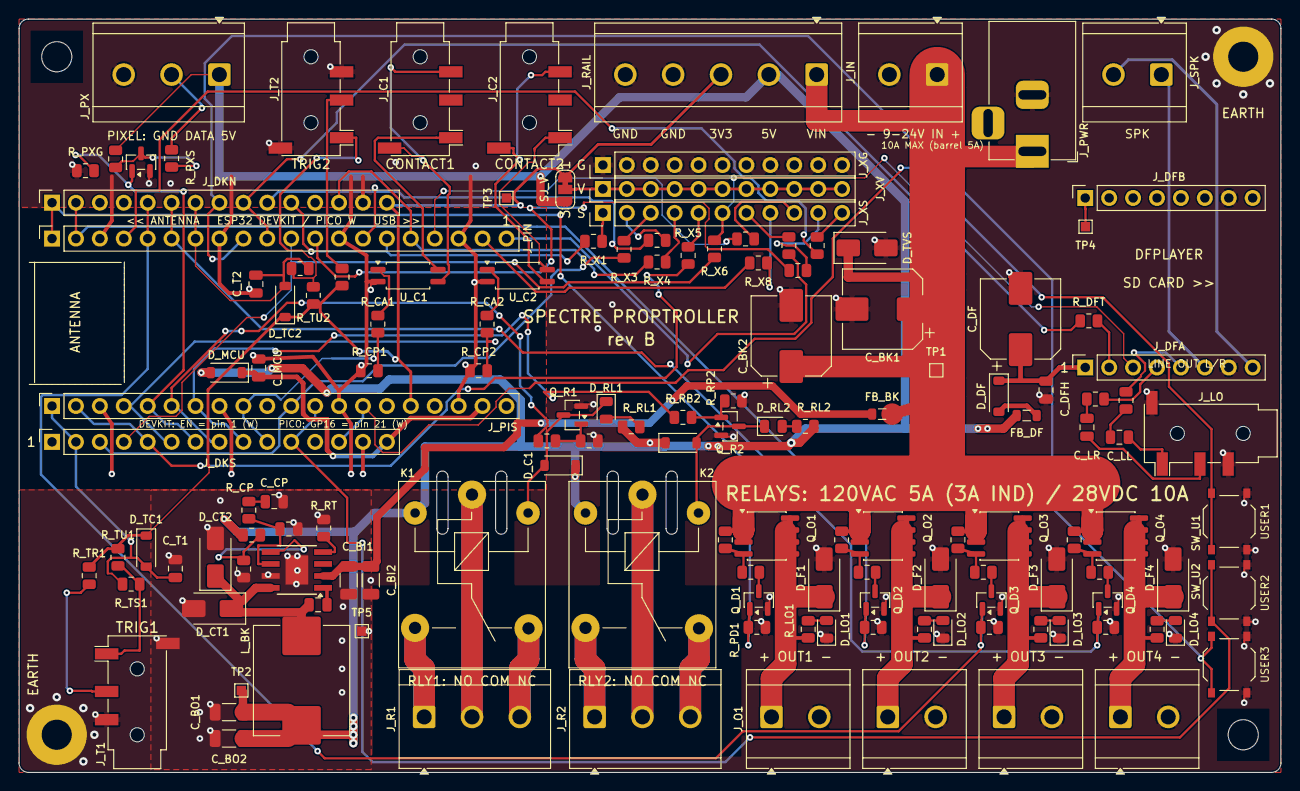
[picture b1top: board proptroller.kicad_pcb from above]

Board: 2 copper layers, 134.0 x 80.0 mm, 145 parts (0 on the bottom side), 102 nets.

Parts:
C_BI1, C_BI2: 10u/50V; C_1206_3216Metric
C_BK1, C_BK2: 100u/50V; CP_Elec_8x10
C_BO1, C_BO2: 47u/10V; C_1206_3216Metric
C_BST: 100n; C_0805_2012Metric
C_CF: 47p/50V; C_0805_2012Metric
C_CP: 6.8n/50V; C_0805_2012Metric
C_DF: 100u/50V; CP_Elec_8x10
C_DFH: 100n; C_0805_2012Metric
C_LL: 10u; C_0805_2012Metric
C_LR: 10u; C_0805_2012Metric
C_MCU: 100n; C_0805_2012Metric
C_T1, C_T2: 100n; C_0805_2012Metric
D_C1, D_C2: B5819W; D_SOD-123
D_CT1, D_CT2: SS56; D_SMA
D_DF: B5819W; D_SOD-123
D_F1, D_F2, D_F3, D_F4: SS56; D_SMA
D_LO1, D_LO2, D_LO3, D_LO4: green; LED_0805_2012Metric
D_MCU: B5819W; D_SOD-123
D_RL1, D_RL2: green; LED_0805_2012Metric
D_TC1, D_TC2: 1N4148W; D_SOD-123
D_TVS: SMAJ24A; D_SMA
FB_BK: 220R@100M 3A; L_0805_2012Metric
FB_DF: 220R@100M 3A; L_0805_2012Metric
H1, H4: M3; MountingHole_3.2mm_M3
H2, H3: M3; MountingHole_3.2mm_M3_Pad
J_C1, J_C2: PJ-320D; Jack_3.5mm_PJ320D_Horizontal
J_DFA: 1x8 socket (DNP); PinSocket_1x08_P2.54mm_Vertical
J_DFB: 1x8 socket (DNP); PinSocket_1x08_P2.54mm_Vertical
J_DKN: 1x15 socket (DNP); PinSocket_1x15_P2.54mm_Vertical
J_DKS: 1x15 socket (DNP); PinSocket_1x15_P2.54mm_Vertical
J_IN: 5.08-2P (DNP); TerminalBlock_CUI_TB007-508-02_1x02_P5.08mm_Horizontal
J_LO: PJ-320D; Jack_3.5mm_PJ320D_Horizontal
J_O1, J_O2, J_O3, J_O4: 5.08-2P (DNP); TerminalBlock_CUI_TB007-508-02_1x02_P5.08mm_Horizontal
J_PIN: 1x20 socket (DNP); PinSocket_1x20_P2.54mm_Vertical
J_PIS: 1x20 socket (DNP); PinSocket_1x20_P2.54mm_Vertical
J_PWR: DC-005-5A-2.0; BarrelJack_Horizontal
J_PX: 5.08-3P (DNP); TerminalBlock_CUI_TB007-508-03_1x03_P5.08mm_Horizontal
J_R1, J_R2: 5.08-3P (DNP); TerminalBlock_CUI_TB007-508-03_1x03_P5.08mm_Horizontal
J_RAIL: 5.08-5P (DNP); TerminalBlock_CUI_TB007-508-05_1x05_P5.08mm_Horizontal
J_SPK: 5.08-2P (DNP); TerminalBlock_CUI_TB007-508-02_1x02_P5.08mm_Horizontal
J_T1, J_T2: PJ-320D; Jack_3.5mm_PJ320D_Horizontal
J_XG: 1x11 pin header (DNP); PinHeader_1x11_P2.54mm_Vertical
J_XS: 1x11 pin header (DNP); PinHeader_1x11_P2.54mm_Vertical
J_XV: 1x11 pin header (DNP); PinHeader_1x11_P2.54mm_Vertical
K1, K2: SRD-05VDC-SL-C; Relay_SPDT_SANYOU_SRD_Series_Form_C
L_BK: 10uH 8.8A; L_Sunlord_MWSA1005S
Q_D1, Q_D2, Q_D3, Q_D4: 2N7002; SOT-23
Q_O1, Q_O2, Q_O3, Q_O4: AO4485; SOIC-8_3.9x4.9mm_P1.27mm
Q_PX: 2N7002; SOT-23
Q_R1, Q_R2: MMBT3904; SOT-23
R_CA1, R_CA2: 220; R_0805_2012Metric
R_CP: 13k; R_0805_2012Metric
R_CP1, R_CP2: 4.7k; R_0805_2012Metric
R_DFT: 1k; R_0805_2012Metric
R_FB1: 43k; R_0805_2012Metric
R_FB2: 8.2k; R_0805_2012Metric
R_GD1, R_GD2, R_GD3, R_GD4: 4.7k; R_0805_2012Metric
R_GS1, R_GS2, R_GS3, R_GS4: 4.7k; R_0805_2012Metric
R_LL: 1k; R_0805_2012Metric
R_LO1, R_LO2, R_LO3, R_LO4: 10k; R_0805_2012Metric
R_LR: 1k; R_0805_2012Metric
R_PD1, R_PD2, R_PD3, R_PD4: 4.7k; R_0805_2012Metric
R_PXG: 4.7k; R_0805_2012Metric
R_PXS: 330; R_0805_2012Metric
R_PXU: 470; R_0805_2012Metric
R_RB1, R_RB2: 1k; R_0805_2012Metric
R_RL1, R_RL2: 1k; R_0805_2012Metric
R_RP1, R_RP2: 4.7k; R_0805_2012Metric
R_RT: 150k; R_0805_2012Metric
R_TR1, R_TR2: 220; R_0805_2012Metric
R_TS1, R_TS2: 4.7k; R_0805_2012Metric
R_TU1, R_TU2: 4.7k; R_0805_2012Metric
R_X1, R_X2, R_X3, R_X4, R_X5, R_X6, R_X7, R_X8, R_X9, R_X10, R_X11: 1k; R_0805_2012Metric
SJ_V: SJ3 1-2; SolderJumper-3_P1.3mm_Bridged12_RoundedPad1.0x1.5mm_NumberL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
SW_U1, SW_U2, SW_U3: TS-1187A; SW_Push_1P1T_XKB_TS-1187A
TP1: +VIN; TestPoint_Pad_1.0x1.0mm
TP2: +5V; TestPoint_Pad_1.0x1.0mm
TP3: +3V3; TestPoint_Pad_1.0x1.0mm
TP4: DF_BUSY; TestPoint_Pad_1.0x1.0mm
TP5: GND; TestPoint_Pad_1.0x1.0mm
U_BK: TPS54360BDDAR; TI_SO-PowerPAD-8
U_C1, U_C2: LTV-217-B-G; SOP-4_4.4x2.6mm_P1.27mm

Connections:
+3V3: D_TC1.1, D_TC2.1, J_DKN.15, J_PIS.16, J_RAIL.3, R_TR1.1, R_TR2.1, R_TU1.1, R_TU2.1, SJ_V.1, TP3.1
+5V: C_BO1.1, C_BO2.1, D_C1.1, D_C2.1, D_MCU.2, FB_DF.1, J_PX.1, J_RAIL.2, K1.2, K2.2, L_BK.2, R_FB1.1, R_PXU.1, R_RL1.1, R_RL2.1, SJ_V.3, TP2.1
+5V_DF: C_DF.1, C_DFH.1, D_DF.1, J_DFA.1
+5V_DFF: D_DF.2, FB_DF.2
+5V_MCU: C_MCU.1, D_MCU.1, J_DKS.15, J_PIS.19
+VIN: C_BK1.1, C_BK2.1, D_TVS.1, FB_BK.1, J_IN.1, J_PWR.1, J_RAIL.1, Q_O1.1, Q_O1.2, Q_O1.3, Q_O2.1, Q_O2.2, Q_O2.3, Q_O3.1, Q_O3.2, Q_O3.3, Q_O4.1, Q_O4.2, Q_O4.3, R_GS1.1, R_GS2.1, R_GS3.1, R_GS4.1, TP1.1
+VIN_BK: C_BI1.1, C_BI2.1, FB_BK.2, U_BK.2
AN_IN: J_DKS.3, J_PIS.11, R_X3.1
BK_BOOT: C_BST.1, U_BK.1
BK_COMP: C_CF.1, R_CP.1, U_BK.6
BK_CZ: C_CP.1, R_CP.2
BK_FB: R_FB1.2, R_FB2.1, U_BK.5
BK_RT: R_RT.1, U_BK.4
BK_SW: C_BST.2, D_CT1.1, D_CT2.1, L_BK.1, U_BK.8
CA1: R_CA1.2, U_C1.1
CA2: R_CA2.2, U_C2.1
COIL1: D_C1.2, D_RL1.1, K1.5, Q_R1.3
COIL2: D_C2.2, D_RL2.1, K2.5, Q_R2.3
CON1: J_DKS.10, J_PIS.9, R_CA1.1, R_CP1.1
CON2: J_DKS.6, J_PIS.4, R_CA2.1, R_CP2.1
CT1_A: J_C1.T, U_C1.4
CT1_B: J_C1.R2, J_C1.S, U_C1.3
CT2_A: J_C2.T, U_C2.4
CT2_B: J_C2.R2, J_C2.S, U_C2.3
DAC_L: J_DFA.5, R_LL.1
DAC_R: J_DFA.4, R_LR.1
DF_BUSY: J_DFB.1, TP4.1
DF_RX: J_DFA.2, R_DFT.2
DF_TX: J_DKN.9, J_PIN.10, R_DFT.1
EXP15: J_DKN.13, J_PIN.16, R_X4.1
EXP34: J_DKS.4, J_PIN.11, R_X6.1
EXP35: J_DKS.5, J_PIS.2, R_X5.1
EXP_GP0: J_PIN.20, R_X7.1
EXP_GP1: J_PIN.19, R_X8.1
EXP_GP2: J_PIN.17, R_X9.1
EXP_GP6: J_PIN.12, R_X10.1
EXP_GP13: J_PIN.4, R_X11.1
G1: Q_O1.4, R_GD1.1, R_GS1.2
G2: Q_O2.4, R_GD2.1, R_GS2.2
G3: Q_O3.4, R_GD3.1, R_GS3.2
G4: Q_O4.4, R_GD4.1, R_GS4.2
GD1: Q_D1.3, R_GD1.2
GD2: Q_D2.3, R_GD2.2
GD3: Q_D3.3, R_GD3.2
GD4: Q_D4.3, R_GD4.2
GND: C_BI1.2, C_BI2.2, C_BK1.2, C_BK2.2, C_BO1.2, C_BO2.2, C_CF.2, C_CP.2, C_DF.2, C_DFH.2, C_MCU.2, C_T1.2, C_T2.2, D_CT1.2, D_CT2.2, D_F1.2, D_F2.2, D_F3.2, D_F4.2, D_LO1.1, D_LO2.1, D_LO3.1, D_LO4.1, D_TVS.2, H2.1, H3.1, J_DFA.7, J_DFB.7, J_DKN.14, J_DKS.14, J_IN.2, J_LO.R2, J_LO.S, J_O1.2, J_O2.2, J_O3.2, J_O4.2, J_PIN.3, J_PIN.8, J_PIN.13, J_PIN.18, J_PIS.3, J_PIS.8, J_PIS.13, J_PIS.18, J_PWR.2, J_PX.3, J_RAIL.4, J_RAIL.5, J_T1.R2, J_T1.S, J_T2.R2, J_T2.S, J_XG.1, J_XG.2, J_XG.3, J_XG.4, J_XG.5, J_XG.6, J_XG.7, J_XG.8, J_XG.9, J_XG.10, J_XG.11, Q_D1.2, Q_D2.2, Q_D3.2, Q_D4.2, Q_PX.2, Q_R1.2, Q_R2.2, R_CP1.2, R_CP2.2, R_FB2.2, R_PD1.2, R_PD2.2, R_PD3.2, R_PD4.2, R_PXG.2, R_RP1.2, R_RP2.2, R_RT.2, SW_U1.2, SW_U2.2, SW_U3.2, TP5.1, U_BK.7, U_BK.9, U_C1.2, U_C2.2
LINE_L: C_LL.2, J_LO.T
LINE_R: C_LR.2, J_LO.R1
LL1: C_LL.1, R_LL.2
LO1: D_LO1.2, R_LO1.2
LO2: D_LO2.2, R_LO2.2
LO3: D_LO3.2, R_LO3.2
LO4: D_LO4.2, R_LO4.2
LR1: C_LR.1, R_LR.2
OUT1: D_F1.1, J_O1.1, Q_O1.5, Q_O1.6, Q_O1.7, Q_O1.8, R_LO1.1
OUT2: D_F2.1, J_O2.1, Q_O2.5, Q_O2.6, Q_O2.7, Q_O2.8, R_LO2.1
OUT3: D_F3.1, J_O3.1, Q_O3.5, Q_O3.6, Q_O3.7, Q_O3.8, R_LO3.1
OUT4: D_F4.1, J_O4.1, Q_O4.5, Q_O4.6, Q_O4.7, Q_O4.8, R_LO4.1
PIXEL: J_DKS.7, J_PIS.5, Q_PX.1, R_PXG.1
PIX_D5: Q_PX.3, R_PXS.1, R_PXU.2
PIX_DATA: J_PX.2, R_PXS.2
PWM1: J_DKN.1, J_PIN.1, Q_D1.1, R_PD1.1
PWM2: J_DKN.2, J_PIN.2, Q_D2.1, R_PD2.1
PWM3: J_DKN.5, J_PIN.5, Q_D3.1, R_PD3.1
PWM4: J_DKN.6, J_PIN.6, Q_D4.1, R_PD4.1
R1_COM: J_R1.2, K1.1
R1_NC: J_R1.3, K1.4
R1_NO: J_R1.1, K1.3
R2_COM: J_R2.2, K2.1
R2_NC: J_R2.3, K2.4
R2_NO: J_R2.1, K2.3
RB1: Q_R1.1, R_RB1.2, R_RP1.1
RB2: Q_R2.1, R_RB2.2, R_RP2.1
RLED1: D_RL1.2, R_RL1.2
RLED2: D_RL2.2, R_RL2.2
RLY1: J_DKS.8, J_PIS.6, R_RB1.1
RLY2: J_DKS.9, J_PIS.7, R_RB2.1
SCL: J_DKN.10, J_PIN.14, R_X2.1
SDA: J_DKN.11, J_PIN.15, R_X1.1
SPK1: J_DFA.8, J_SPK.2
SPK2: J_DFA.6, J_SPK.1
T1_RING: J_T1.R1, R_TR1.2
T1_TIP: J_T1.T, R_TS1.1, R_TU1.2
T2_RING: J_T2.R1, R_TR2.2
T2_TIP: J_T2.T, R_TS2.1, R_TU2.2
TRIG1: C_T1.1, D_TC1.2, J_DKS.2, J_PIS.1, R_TS1.2
TRIG2: C_T2.1, D_TC2.2, J_DKN.7, J_PIN.7, R_TS2.2
USER1: J_DKS.13, J_PIS.14, SW_U1.1
USER2: J_DKS.11, J_PIS.12, SW_U2.1
USER3: J_DKN.8, J_PIN.9, SW_U3.1
V_EXP: J_XV.1, J_XV.2, J_XV.3, J_XV.4, J_XV.5, J_XV.6, J_XV.7, J_XV.8, J_XV.9, J_XV.10, J_XV.11, SJ_V.2
XS1: J_XS.1, R_X1.2
XS2: J_XS.2, R_X2.2
XS3: J_XS.3, R_X3.2
XS4: J_XS.4, R_X4.2
XS5: J_XS.5, R_X5.2
XS6: J_DFA.3, J_XS.6, R_X6.2
XS7: J_XS.7, R_X7.2
XS8: J_XS.8, R_X8.2
XS9: J_XS.9, R_X9.2
XS10: J_XS.10, R_X10.2
XS11: J_XS.11, R_X11.2

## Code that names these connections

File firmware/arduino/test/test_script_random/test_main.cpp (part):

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  uint32_t range(uint32_t a, uint32_t b) { return a + below(b - a + 1); }
};

const char* const INPUTS[INPUT_COUNT] = {"trig1", "trig2", "user1", "user2", "user3"};
const char* const OUTS[CHANNEL_COUNT] = {"out1", "out2", "out3", "out4", "rly1", "rly2", "cc1", "cc2"};

struct Gen {
  std::string text;
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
